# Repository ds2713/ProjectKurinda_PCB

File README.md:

# ProjectKurinda_PCB
This repository contains the PCB design data for the Project Kurinda landslide sensor.

## Introduction

The PCB has been specifically designed to be simple to understand for beginners, while also being extremely cheap to manufacture. All of the modules are basic Arduino development boards which can be soldered onto the base PCB by hand.

Over time, this PCB will be developed further to offer users the choice between using the Arduino development board sensors (for simplicity and educational purposes), or using the underlying components soldered directly onto the PCB to minimise costs further and shrink the sensor.

## Architecture

As with all designs like this, there are many options to choose from with various advantages and disadvantages. The following components were chosen for this version for a variety of reasons including cost, availability, interface simplicity, and additional features. Most sensors could be replaced with similar components with minimal rework.

### Microcontroller

The landslide sensor is based around the ESP32-C3 Supermini microcontroller development board. These boards provide a reasonable number of GPIO ports, analogue inputs, as well as i2c and SPI connections for some of the sensors. They also provide WiFi connectivity natively, which is used in this version for development and transmitting sensor readings (but will be superceded by LoRa technologies in the future).

The software for these boards can be developed within the Arduino ecosystem, which provides a large support community and many users will already be familiar with. This will help the Project Kurinda ecosystem improve over time, as the community can contribute improvements.

These development boards can be purchased cheaply from many sources, which will hopefully help with the international uptake of this project. By keeping the design basic (for example using a two layer PCB), they should be easy to manufacture and assemble by hand.

## Sensors

The first version of the sensor (v1.0) used standard Arduino modules to measure the temperature, humidity, acceleration and soil moisture. Although these sensors worked sufficiently well for the first prototype, they all had various issues which made them undesirable for the new design. One of the biggest challenges was power consumption, with the sensors drawing current all the time even when not collecting readings. On the second version of the sensor (v1.1), the modules were replaced with components which draw much less power. Additionally, a simple switch was added to the sensor to turn off the 3.3 V rail to the sensors when they are not required (for example, when the sensor is asleep between readings). This massively reduces the power consumption of the system, and will allow it to either last longer on battery power, or use a smaller battery plus solar panel to save cost.

All of the sensors chosen (with the exception of the generic soil moisture probe) can be bought as individual integrated circuits (cheaper) or as ready-made breakout boards (easier to assembly by hand). This allows the same sensor architecture and software to be used across sensor designs, whether that is the larger sensor for manual assembly or the smaller sensor planned in the future for automated assembly.

### Temperature and humidity sensor

Originally, the DHT11 temperature and humidity sensor was chosen. However, this sensor has various limitations and is a relatively old component. For example, the sample rate is limited to around once per second, and the serial interface was fairly unreliable during development tests.

In the second version of the PCB, this sensor was replaced with the **SHT40** sensor from Sensirion. The sensor provides an i2c interface for retrieving the readings like the DHT11, but has no 1 Hz limit and has a much better temperature sensitivity.

| Parameter                         | Value               |
|-----------------------------------|---------------------|
| **Humidity**                      |                     |
| Typ. relative humidity accuracy   | 1.8 %RH             |
| Operating relative humidity range | 0 - 100 %RH         |
| Response time (τ63%)              | 4	s                 |
| Calibration certificate           | Factory calibration |
| **Temperature**                   |                     |
| Typ. temperature accuracy         | 0.2 °C              |
| Response time (τ63%)              | 2	s                 |

### Accelerometer

There are lots of accelerometer sensors available for Arduino projects. In the first version, the MPU6050 was used but this was replaced by the **LIS2DW12** from ST Microelectronics in the latest design. The largest improvement here is the low power mode of the accelerometer, which the datasheet lists as 1 µA in active low-power mode.

| Parameter                  | Value                                                         |
|----------------------------|---------------------------------------------------------------|
| Ultralow power consumption | 50 nA in power-down mode, below 1 µA in active low-power mode |
| Noise                      | Down to 1.3 mg RMS in low-power mode                          |
| Supply voltage             | 1.62 V to 3.6 V                                               |
| Acceleration range         | ±2g/±4g/±8g/±16g full scale                                   |

This accelerometer also provides two interrupt outputs, which will allow the accelerometer to alert the microcontroller if it detects motion. This will help the sensor to reduce its power consumption even further, because the microcontroller can be put into sleep mode and then awoken by the accelerometer.

### Real-Time Clock (RTC)

The sensors use the RTC to timestamp the sensor readings.

The RTC can also be configured to provide an interrupt to the microcontroller, at a chosen interval. This will be used to wake the microcontroller from  sleep to take a sensor reading. Turning off the sensors and putting the microcontroller into deep sleep mode allows the landlide sensor to minimise its power consumption.

The first prototype used a generic RTC module, but this was replaced on the latest version of the board by the **RV3028** RTC from Microcrystal. This device is fully integrated with the crystal, and is specifically designed to be ultra low power draw (~ 100 nA). This should allow the RTC to operate from a tiny battery for an extremely long time (many years).

| Parameter    | Value                                             |
|--------------|---------------------------------------------------|
| Current draw | ~100nA typical                                    |
| Accuracy     | ±1 second drift per million seconds at 25 degrees |

The accuracy of this RTC means that it should only drift by around 1 second every 11.5 days (around 31 seconds per year). This is important because the timekeeping will be used to tell the sensor when to transmit its readings on the wireless network.

### Soil Moisture Sensor

The soil moisture sensor is the only sensor which remained the same between versions of the board, partly because it is cheap and easy to use, and easily available. Better sensors are considerably more expensive or would be harder to interface with, so it was decided to keep the same sensor.

The soil moisture sensor is the component with the largest power draw, because it is based around a relatively old timing chip providing the high frequency signal to the capacitive probe. However, this sensor is only required for short periods of time to monitor the soil moisture when the microcontroller needs a reading, so it can be turned off for the rest of the time and only use power for a few seconds when the reading is taken.

These soil moisture sensors can be purchased from many places, but one example listing on eBay is provided below.

https://www.ebay.co.uk/itm/205646455998

### Micro SD card

The micro SD card is used to store the sensor readings for long duration. This isn't strictly necessary for the sensor if the wireless network is operating properly and the readings are transmitted quickly, but if the microcontroller loses power or can't transmit for some reason, the recent readings would be lost. The micro SD card allows the sensor to store the readings until either the wireless network is operating again, or someone can manually collect the data.

On the prototype sensor, the **DFR0229** micro SD module from DFRobot was used, but any breakout board should be adequate.

## Changes from v1.0 to v1.1

Apart from changing the sensor modules themselves, some extra improvements were made to the second version of the sensor (v1.1). These are listed below.

### Power switching

Instead of providing 3.3 V to all the sensors all the time, a small P-channel MOSFET switch was added to the PCB to allow the microcontroller to switch the power rail off when not required. Specifically, this switched rail now provides the power to the soil moisture and the temperature & humidity sensors, and the micro SD card. When the microcontroller wants to take a reading, it can enable this rail to turn on the sensors. After the readings have been collected, the rail can be turned off to save power.

The schematic for this power switch is shown below.

*Power switch on 3.3 V rail to selectively power sensors.*

### Battery voltage monitoring

It is useful for the microcontroller to be able to read its own battery voltage. In the simplest form, this can be achieved by using a potential divider to reduce the raw battery voltage and provide that to an analogue input on the microcontroller. Although this does add a small constant draw on the battery, this can be minimised by using very large resistor values to reduce the current at the expense of higher noise on the signal. However, this should be adequate for a very basic voltage reading to give an indication of the battery level.

*Potential divider on battery voltage rail.*

### Filtering on soil moisture sensor analogue input

The output of the soil moisture sensor is a simple analogue signal, which is connected to the microcontroller through the PCB. This signal should be filtered near the microcontroller input to reduce noise. A simple RC network is used to attentuate any high frequency noise. The component values can be adjusted if necessary, but the existing values give a corner frequency of ~160 Hz which should be a reasonable starting point.

### i2c pull-up resistor footprints

These footprints can be used if the i2c rail needs pulling up for reliable operation. In theory, the various breakout boards already provide these resistors so they shouldn't be necessary, but the footprints have been added to the PCB in case they are required in the future.

## Surface mount components

The battery voltage monitoring, power switching and analogue filtering all require surface mount components to be fitted to the PCB. However, this may be challenging in an educational setting or with users who are new to soldering. Therefore, simple solder jumpers have been added to the PCB to bypass the surface mount components if necessary.

By shorting out solder jumper JP1 on the PCB, the 3.3 V switched rail is directly fed from the 3.3 V main power rail. This means that the microcontroller cannot turn off the sensors to save power, but the sensors can be read by the microcontroller at any time. This should be convenient for educational settings.

Solder jumper JP2 connects the analogue output of the soil moisture sensor directly to the analogue input of the microcontroller (without the filter). This means the signal will be more susceptible to noise, but again it should be perfectly adequate for normal use.

*Solder jumper JP1 to permanently power the 3.3 V switched rail, and JP2 to connect the analogue output from the soil moisture sensor to the analogue input on the microcontroller.*

## PCB design software

The PCB was designed in KiCAD 10.0.

If you wish to view or modify the design, please download KiCAD from https://www.kicad.org/

## PCB manufacture

This prototype was manufactured by Eurocircuits, who generously sponsored this project with funding for the PCBs. We would like to thank Eurocircuits for their support.

https://www.eurocircuits.com/

# Updated sensor modules

The new sensor modules listed above can be purchased on the following links.

1. RTC -> RV3028: https://thepihut.com/products/rv3028-real-time-clock-rtc-breakout
2. T&H -> SHT40: https://thepihut.com/products/adafruit-sensirion-sht40-temperature-humidity-sensor-stemma-qt-qwiic
3. Accelerometer -> LIS2DW12: https://thepihut.com/products/fermion-lis2dw12-triple-axis-accelerometer-sensor-breakout-16g
4. Micro SD card ->  DFR0229: https://thepihut.com/products/microsd-card-module-for-arduino

## Sources

Several of the footprints and models of the development modules have been drawn from online resources. These are listed below.

**Most of these modules have been superceded on the latest sensor design, but these resources have been left here for reference.**

1. ESP32-C3 Supermini:
- Schematic component, PCB footprint, 3D model: https://www.snapeda.com/parts/ESP32-C3%20SuperMini_TH/Espressif+Systems/view-part/?ref=snap

2. Water sensor:
- 3D model: https://grabcad.com/library/water-level-sensor-5
- 3D model: https://grabcad.com/library/capacitive-soil-moisture-sensor-v1-2-2

3. Temperature and humidity sensor:
- 3D model: https://grabcad.com/library/ky-015-dht11-1

4. Accelerometer:
- 3D model: https://grabcad.com/library/mpu6050-accelerometer-module-2

# Next Steps

The next version of the PCB will include the LoRa radio module, and associated support circuitry.

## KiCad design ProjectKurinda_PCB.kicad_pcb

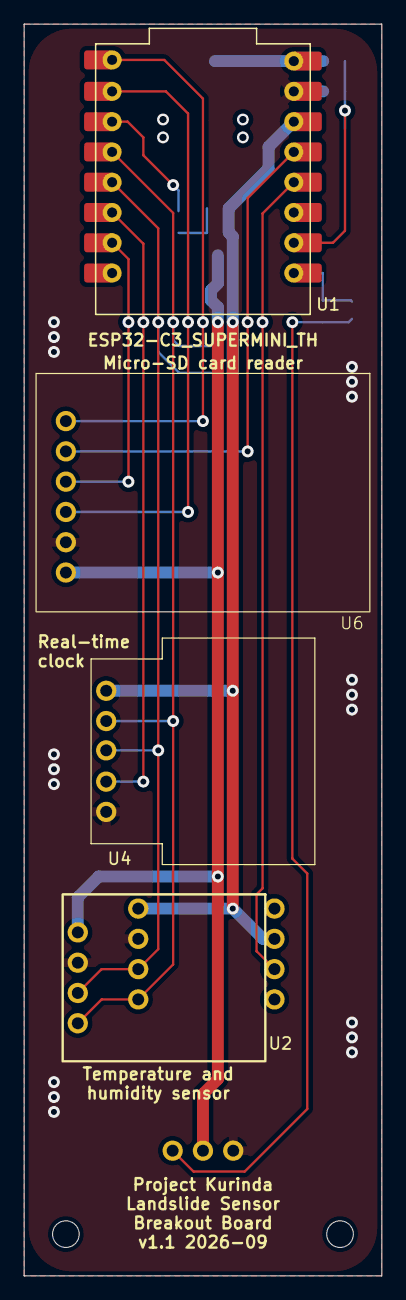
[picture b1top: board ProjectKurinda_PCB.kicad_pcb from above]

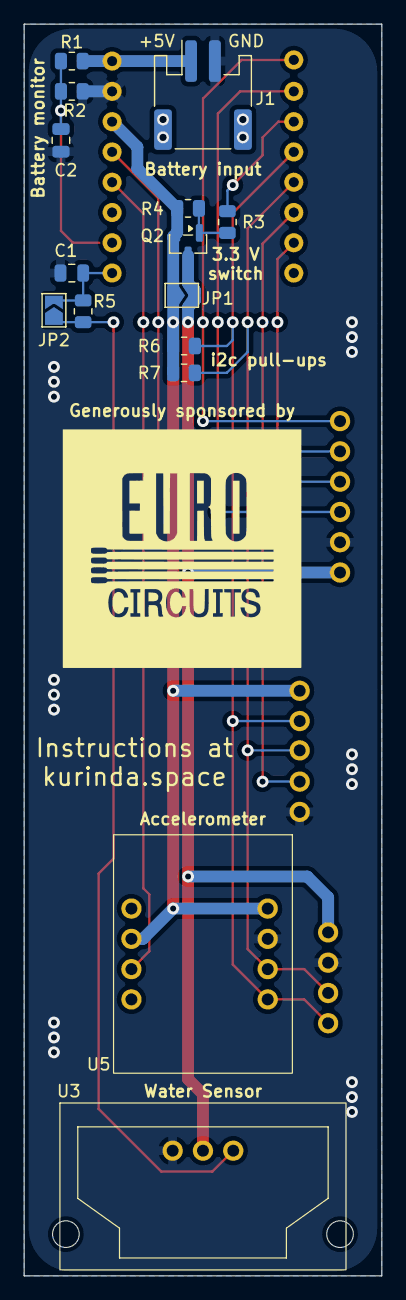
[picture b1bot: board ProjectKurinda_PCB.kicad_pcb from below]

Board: 2 copper layers, 30.0 x 105.0 mm, 19 parts (15 on the bottom side), 17 nets.

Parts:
C1, C2: 1uF; C_0805_2012Metric
J1: Conn_01x02; JST_PH_S2B-PH-SM4-TB_1x02-1MP_P2.00mm_Horizontal
JP1, JP2: Jumper_2_Open; SolderJumper-2_P1.3mm_Open_TrianglePad1.0x1.5mm
Q2: Q_PMOS_GSD; SOT-23
R1: 300 kR; R_0805_2012Metric
R2, R4: 100 kR; R_0805_2012Metric
R3: 1 kR; R_0805_2012Metric
R5: 1kR; R_0805_2012Metric
R6, R7: 4.7kR; R_0805_2012Metric
U1: ESP32-C3_SUPERMINI_TH; ESP32-C3 SUPERMINI TH
U2: SHT40
U3: Water Sensor
U4: RV3028 RTC; RV3028 RTC breakout
U5: LIS2DW12 breakout
U6: uSD breakout

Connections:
+3V3: JP1.1 (A), Q2.2 (S), R4.2, R6.2, R7.2, U1.3.3 (3V3), U4.1 (Vcc), U5.2 (CS), U5.8 (Vcc)
+BATT: J1.1, R1.1, U1.5V
/3V3_EN: R3.1, U1.7 (GPIO7)
/3V3_SWITCHED: JP1.2 (B), Q2.3 (D), U2.1 (Vcc), U3.2 (Vcc), U6.6 (Vcc)
/BAT_MEAS: C2.1, R1.2, R2.1, U1.1 (GPIO1)
/CS: U1.20 (GPIO20), U6.3 (CS)
/MISO: U1.5 (GPIO5), U6.1 (MISO)
/MOSI: U1.6 (GPIO6), U6.4 (MOSI)
/MPU_INT1: U1.3 (GPIO3), U5.3 (INT1)
/RTC_INT: U1.10 (GPIO10), U4.4 (INT)
/SCK: U1.4 (GPIO4), U6.2 (SCK)
/SCL: R7.1, U1.9 (GPIO9), U2.3 (SCL), U4.3 (SCL), U5.6 (SCL)
/SDA: R6.1, U1.8 (GPIO8), U2.4 (SDA), U4.2 (SDA), U5.5 (SDA)
/WS_AOUT: JP2.1 (A), R5.1, U3.1 (A)
GND: C1.2, C2.2, J1.2, R2.2, U1.G (GND), U2.2 (GND), U3.3 (GND), U4.5 (GND), U5.7 (GND), U6.5 (GND)
unnamed: C1.1, JP2.2 (B), R5.2, U1.0 (GPIO0)
unnamed: Q2.1 (G), R3.2, R4.1

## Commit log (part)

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2026-05-22 v1.0 board design for landslide sensor and associated PCB symbols and libraries.
2026-05-25 Added correct soil moisture sensor and updated silk screen to match.
2026-05-25 New 3D model using the correct soil moisture sensor.
